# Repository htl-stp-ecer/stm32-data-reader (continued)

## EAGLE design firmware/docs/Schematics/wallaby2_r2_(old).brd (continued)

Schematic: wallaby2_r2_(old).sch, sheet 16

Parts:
C2, C3, C4, C5, C6, C7, C8, C9, C10, C11, C13, C19, C74: 0.1uF; 0603
C12, C73: 2.2uF; 0603
C16: 10uF; 0805-NO
C17, C18: 1uF; 0805-NO
D1: MBR0540; SOD-123
D2: MM3Z24VT1G; SMADIODE
D3: 1N4148; SOD-323
FB1, FB2, FB3, FB4: Ferrite; _0805MP
J9: 40PINFPCM4-1734839-0; 4-1734839-0
L1: 15uH; INDUCTOR_5X5MM_NR5040_NOTHERMALS
R1, R2, R3, R4, R5, R8: 10k; 0603
R6, R67, R72, R73: 0; 0603
R7: 47k; 0603
R15, R16: 12; 0805-NO
R70, R71: DNP; 0603
SJ1, SJ2: SOLDERJUMPER; SOLDERJUMPER_ARROW_NOPASTE
SJ3: -25mA; SOLDERJUMPER_CLOSEDWIRE
U1: TFP401; S-PQFP-G100
U2: 24LC02BT-I/OT; SOT23-5
U4: FAN5333BSX; SOT23-5
U31, U32, U33, U34: MOUNTINGHOLE3.0; MOUNTINGHOLE_3.0_PLATED
U$8: TSC2003; TSSOP16
X1: 47151-0001; HDMI_MOLEX_47151-0001_DIMLAYER

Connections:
5.0V: C13.1, R1.1, R3.2, R4.2, U2.4 (VCC), X1.18 (+5V)
24V: C17.1, C18.1, D1.C, D2.C, J9.2 (MS)
ACTIVE: D3.C, J9.31 (MS), U1.8 (SCDT)
AVDD: C9.1, C11.1, FB3.2, U1.82 (AVDD), U1.84 (AVDD), U1.88 (AVDD), U1.95 (AVDD)
B0: J9.21 (MS), U1.10 (QE0)
B1: J9.22 (MS), U1.11 (QE1)
B2: J9.23 (MS), U1.12 (QE2)
B3: J9.24 (MS), U1.13 (QE3)
B4: J9.25 (MS), U1.14 (QE4)
B5: J9.26 (MS), U1.15 (QE5)
B6: J9.27 (MS), U1.16 (QE6)
B7: J9.28 (MS), U1.17 (QE7)
CTL1: U1.40 (CTL1)
CTL2: U1.41 (CTL2)
CTL3: U1.42 (CTL3)
DISPEN: J9.34 (MS), U1.46 (DE)
G0: J9.13 (MS), U1.20 (QE8)
G1: J9.14 (MS), U1.21 (QE9)
G2: J9.15 (MS), U1.22 (QE10)
G3: J9.16 (MS), U1.23 (QE11)
G4: J9.17 (MS), U1.24 (QE12)
G5: J9.18 (MS), U1.25 (QE13)
G6: J9.19 (MS), U1.26 (QE14)
G7: J9.20 (MS), U1.27 (QE15)
GND: C2.2, C3.2, C4.2, C5.2, C6.2, C7.2, C8.2, C9.2, C10.2, C11.2, C12.2, C13.2, C16.1, C17.2, C18.2, C19.2, C73.2, C74.2, J9.3 (MS), J9.29 (MS), J9.36 (MS), R5.1, R15.2, R16.2, R72.2, R73.2, SJ2.1, U1.1 (DFO), U1.4 (PIXS), U1.5 (GND), U1.19 (OGND), U1.28 (OGND), U1.39 (GND), U1.45 (OGND), U1.58 (OGND), U1.68 (GND), U1.76 (OGND), U1.79 (AGND), U1.83 (AGND), U1.87 (AGND), U1.89 (AGND), U1.92 (AGND), U1.98 (PGND), U1.P$1 (TP), U1.P$2 (TP), U1.P$3 (TP), U1.P$4 (TP), U1.P$5 (TP), U1.P$6 (TP), U1.P$7 (TP), U1.P$8 (TP), U1.P$9 (TP), U1.P$10 (TP), U1.P$11 (TP), U1.P$12 (TP), U1.P$13 (TP), U1.P$14 (TP), U1.P$15 (TP), U1.P$16 (TP), U1.THERMAL (TP), U2.2 (GND), U2.5 (WP), U4.2 (GND), U$8.P$6 (6_GND), X1.2 (TX2_SHIELD), X1.5 (TX1_SHIELD), X1.8 (TX0_SHIELD), X1.11 (TXC_SHIELD), X1.17 (GND), X1.P$1 (GND), X1.P$2 (GND), X1.P$3 (GND), X1.P$4 (GND); also elsewhere on the board
HSYNC: J9.32 (MS), U1.48 (HSYNC)
LEDK: C19.1, D2.A, J9.1 (MSV), R16.1, SJ3.2, U4.3 (FB)
unnamed: U1.93 (RXC+), X1.10 (TXC+)
unnamed: U1.94 (RXC-), X1.12 (TXC-)
unnamed: U1.90 (RX0+), X1.7 (TX0+)
unnamed: U1.91 (RX0-), X1.9 (TX0-)
unnamed: U1.85 (RX1+), X1.4 (TX1+)
unnamed: U1.86 (RX1-), X1.6 (TX1-)
unnamed: U1.80 (RX2+), X1.1 (TX2+)
unnamed: U1.81 (RX2-), X1.3 (TX2-)
unnamed: R1.2, X1.19 (HOTPLUG)
unnamed: R67.1, U$8.P$7 (7_VBAT1)
unnamed: C73.1, C74.1, R6.2, U$8.P$9 (9_VREF)
unnamed: R71.2, R73.1, U$8.P$13 (13_A1)
unnamed: D1.A, L1.P$2 (2), U4.1 (SW)
unnamed: R15.1, SJ3.1
unnamed: D3.A, R8.1, U4.4 (SHDN)
unnamed: R70.2, R72.1, U$8.P$14 (14_A0)
OCK_INV: R5.2, SJ1.1, U1.100 (OCK_INV)
OVDD: C5.1, C6.1, C7.1, C8.1, FB2.2, U1.18 (OVDD), U1.29 (OVDD), U1.43 (OVDD), U1.57 (OVDD), U1.78 (OVDD)
PIXCLK: J9.30 (MS), U1.44 (ODCK)
PI_GPIO25: R7.2, U$8.P$10 (10_PEN); also elsewhere on the board
PI_I2C1_SCL: U$8.P$12 (12_SCL); also elsewhere on the board
PI_I2C1_SDA: U$8.P$11 (11_SDA); also elsewhere on the board
PVDD: C10.1, FB4.2, U1.97 (PVDD)
PWRDN: U1.2 (#PD)
PWRDN_O: U1.9 (#PDO)
R0: J9.5 (MS), U1.30 (QE16)
R1: J9.6 (MS), U1.31 (QE17)
R2: J9.7 (MS), U1.32 (QE18)
R3: J9.8 (MS), U1.33 (QE19)
R4: J9.9 (MS), U1.34 (QE20)
R5: J9.10 (MS), U1.35 (QE21)
R6: J9.11 (MS), U1.36 (QE22)
R7: J9.12 (MS), U1.37 (QE23)
SCL: R4.1, U2.1 (SCL), X1.15 (DCLK)
SDA: R3.1, U2.3 (SDA), X1.16 (DDAT)
ST: R2.1, SJ2.2, U1.3 (ST)
VCC_3V3: C4.1, C12.1, FB1.1, FB2.1, FB3.1, FB4.1, J9.4 (MS), R6.1, R7.1, R67.2, R70.1, R71.1, U$8.P$1 (1_VDD); also elsewhere on the board
VCC_5V0: C16.2, L1.P$1 (1), R8.2, U4.5 (VIN); also elsewhere on the board
VDDIO: C2.1, C3.1, FB1.2, R2.2, SJ1.2, U1.6 (DVDD), U1.7 (#STAG), U1.38 (DVDD), U1.67 (DVDD), U1.99 (RSVD)
VSYNC: J9.33 (MS), U1.47 (VSYNC)
X+: J9.37 (MS), U$8.P$2 (2_XP)
X-: J9.39 (MS), U$8.P$4 (4_XN)
Y+: J9.38 (MS), U$8.P$3 (3_YP)
Y-: J9.40 (MS), U$8.P$5 (5_XP)

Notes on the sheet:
DNP

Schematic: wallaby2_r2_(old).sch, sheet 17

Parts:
FID1, FID2, FID3, FID4, FID5, FID6: FIDUCIAL1X2.5; FIDUCIAL-1X2.5

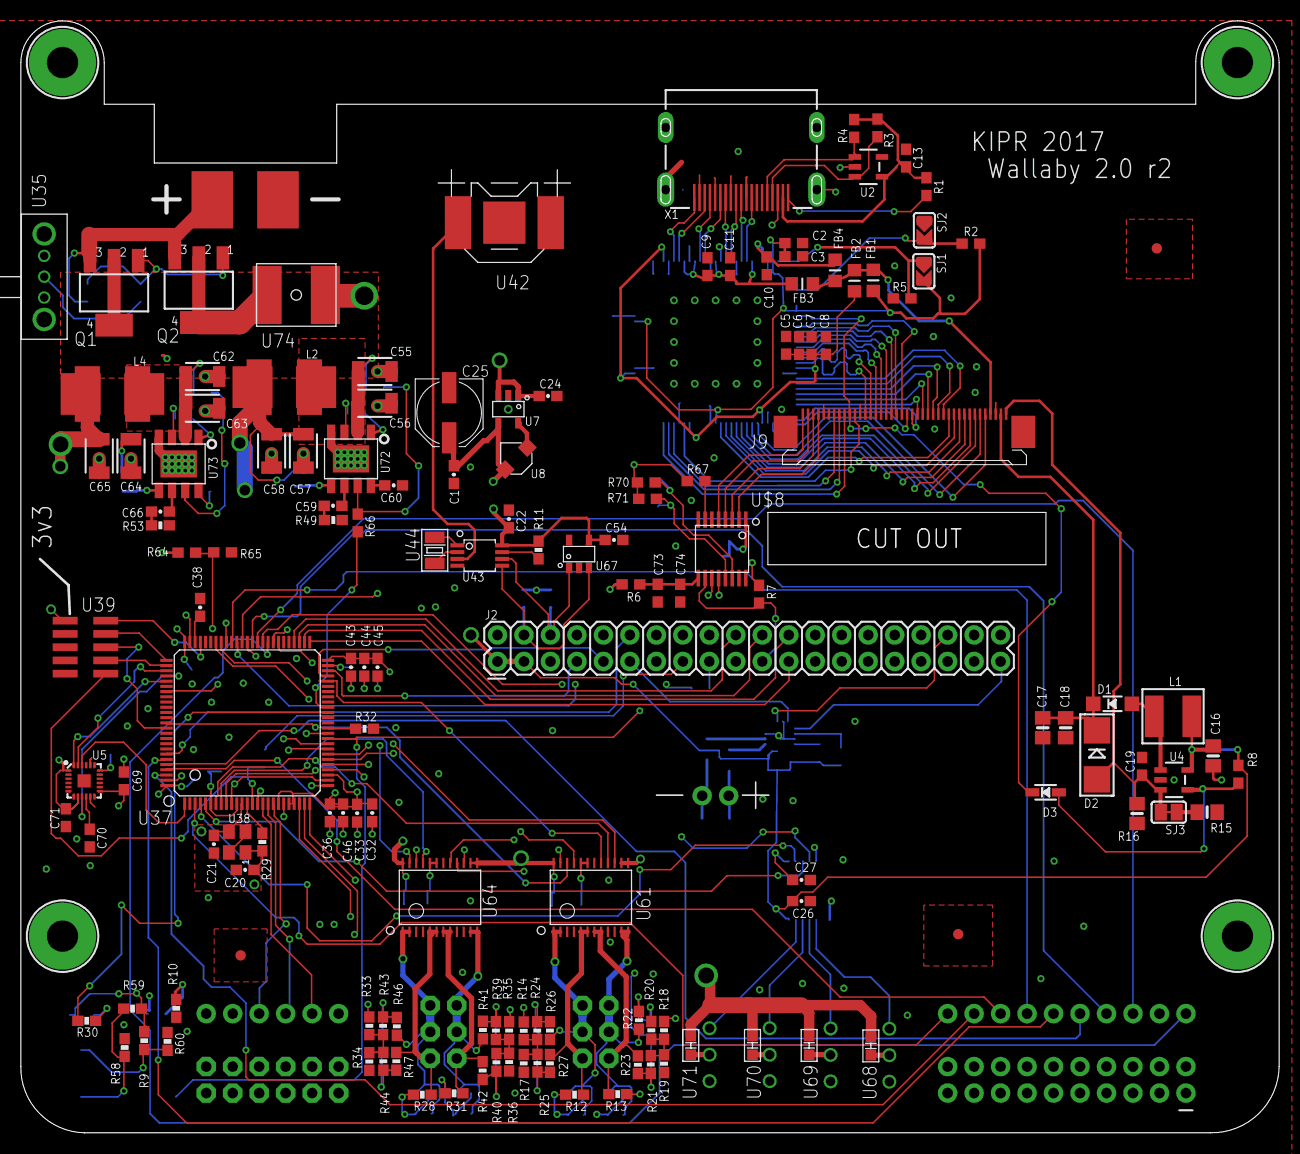
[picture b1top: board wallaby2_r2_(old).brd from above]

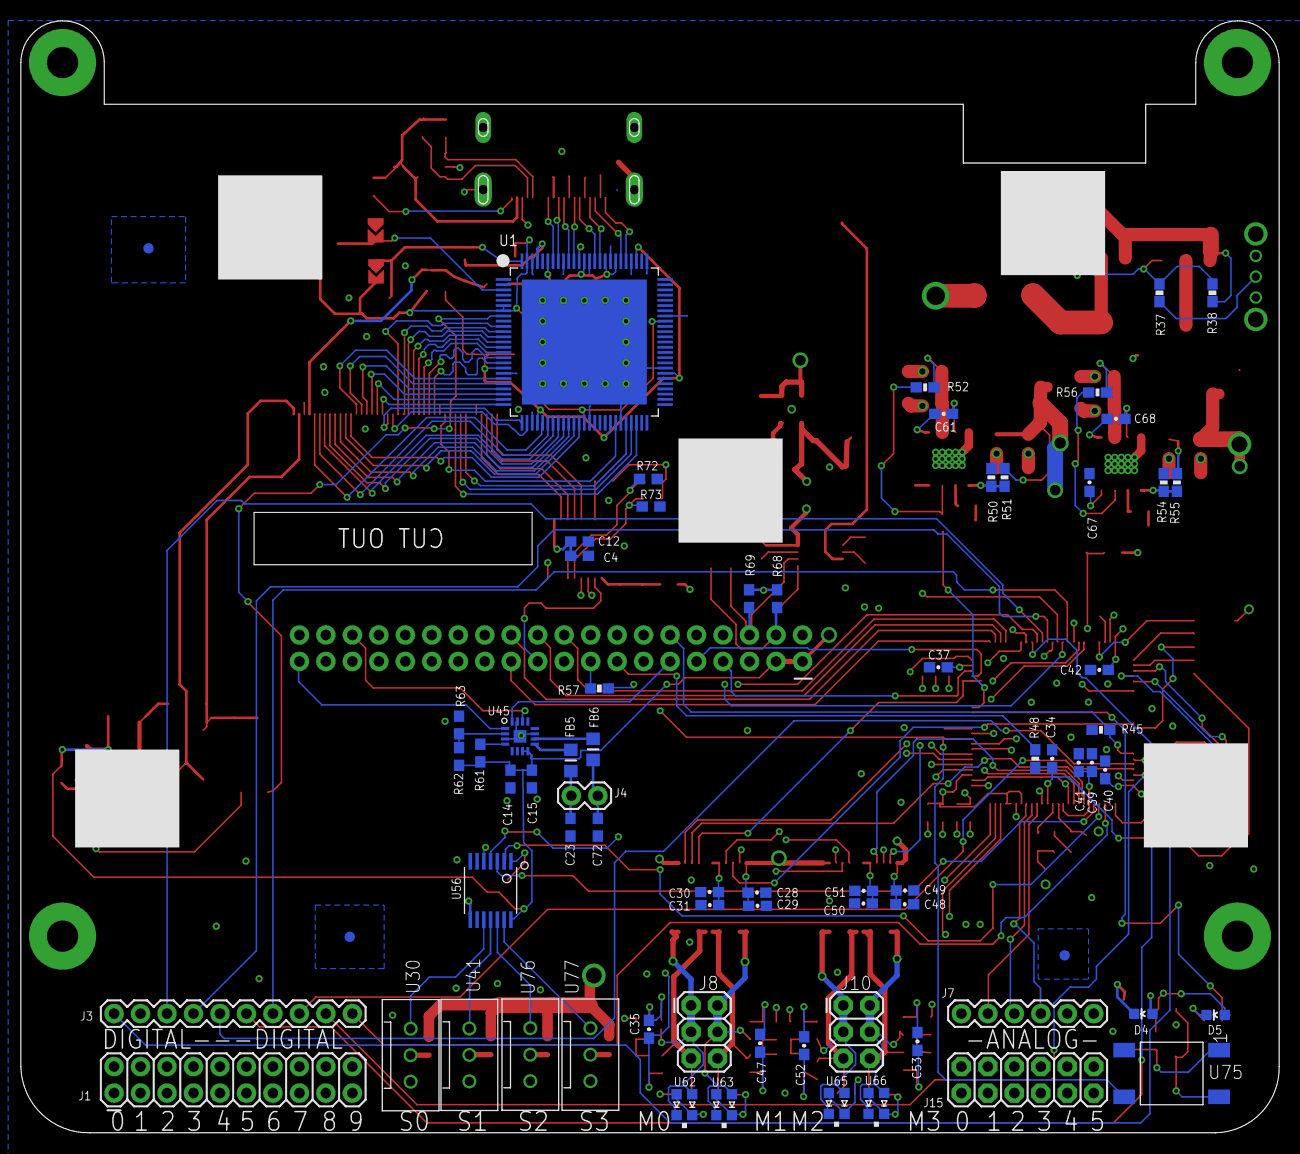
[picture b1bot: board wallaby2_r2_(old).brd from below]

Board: 6 copper layers, 120.7 x 106.7 mm, 222 parts (71 on the bottom side), 198 nets.

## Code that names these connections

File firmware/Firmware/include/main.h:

/* USER CODE BEGIN Header */
/**
  ******************************************************************************
  * @file           : main.h
  * @brief          : Header for main.c file.
  *                   This file contains the common defines of the application.
  ******************************************************************************
  * @attention
  *
  * Copyright (c) 2025 STMicroelectronics.
  * All rights reserved.
  *
  * This software is licensed under terms that can be found in the LICENSE file
  * in the root directory of this software component.
  * If no LICENSE file comes with this software, it is provided AS-IS.
  *
  ******************************************************************************
  */
/* USER CODE END Header */

/* Define to prevent recursive inclusion -------------------------------------*/
#ifndef __MAIN_H
#define __MAIN_H

#ifdef __cplusplus
extern "C" {
#endif

/* Includes ------------------------------------------------------------------*/
#include "stm32f4xx_hal.h"

/* Exported types ------------------------------------------------------------*/

/* Exported constants --------------------------------------------------------*/

/* Exported macro ------------------------------------------------------------*/

/* Exported functions prototypes ---------------------------------------------*/
void Error_Handler(void);


/* Private defines -----------------------------------------------------------*/
/*----------<user LED>----------*/
#define USER_LED_Pin GPIO_PIN_9
#define USER_LED_GPIO_Port GPIOE

/*----------<SPI>----------*/
//SPI for IMU
#define IMU_SPI_CS0_Pin GPIO_PIN_2
#define IMU_SPI_CS0_GPIO_Port GPIOE
#define IMU_SPI_CS1_Pin GPIO_PIN_3
#define IMU_SPI_CS1_GPIO_Port GPIOE
#define IMU_SPI_SCK_Pin GPIO_PIN_10
#define IMU_SPI_SCK_GPIO_Port GPIOC
#define IMU_SPI_MISO_Pin GPIO_PIN_11
#define IMU_SPI_MISO_GPIO_Port GPIOC
#define IMU_SPI_MOSI_Pin GPIO_PIN_12
#define IMU_SPI_MOSI_GPIO_Port GPIOC

//SPI communication with the Raspberry Pi
#define PI_SPI_CS_Pin GPIO_PIN_12
#define PI_SPI_CS_GPIO_Port GPIOB
#define PI_SPI_SCK_Pin GPIO_PIN_13
#define PI_SPI_SCK_GPIO_Port GPIOB
#define PI_SPI_MISO_Pin GPIO_PIN_14
#define PI_SPI_MISO_GPIO_Port GPIOB
#define PI_SPI_MOSI_Pin GPIO_PIN_15
#define PI_SPI_MOSI_GPIO_Port GPIOB

/*----------<UART>----------*/
//UART communication with the Raspberry Pi
#define PI_UART_TX_Pin GPIO_PIN_10
#define PI_UART_TX_GPIO_Port GPIOB

#define PI_UART_RX_Pin GPIO_PIN_11
#define PI_UART_RX_GPIO_Port GPIOB

/*----------<Servo>----------*/
//6V0 Enable (Servo Voltage Source)
#define SERVO_6V0_ENABLE_Pin GPIO_PIN_10
#define SERVO_6V0_ENABLE_GPIO_Port GPIOE

//servo PWM pins
#define S0_PWM_Pin GPIO_PIN_8
#define S0_PWM_GPIO_Port GPIOC

#define S1_PWM_Pin GPIO_PIN_7
#define S1_PWM_GPIO_Port GPIOC

#define S2_PWM_Pin GPIO_PIN_6
#define S2_PWM_GPIO_Port GPIOE

#define S3_PWM_Pin GPIO_PIN_5
#define S3_PWM_GPIO_Port GPIOE

/*----------<motor>----------*/
//motor PWM pins
#define MOT0_PWM_Pin GPIO_PIN_8
#define MOT0_PWM_GPIO_Port GPIOA

#define MOT1_PWM_Pin GPIO_PIN_9
#define MOT1_PWM_GPIO_Port GPIOA

#define MOT2_PWM_Pin GPIO_PIN_10
#define MOT2_PWM_GPIO_Port GPIOA

#define MOT3_PWM_Pin GPIO_PIN_6
#define MOT3_PWM_GPIO_Port GPIOC

//motor direction pins
//motor 0 direction pins
#define MOT0_D0_Pin GPIO_PIN_1
#define MOT0_D0_GPIO_Port GPIOD
#define MOT0_D1_Pin GPIO_PIN_7
#define MOT0_D1_GPIO_Port GPIOD

//motor 1 direction pins
#define MOT1_D1_Pin GPIO_PIN_13
#define MOT1_D1_GPIO_Port GPIOC
#define MOT1_D0_Pin GPIO_PIN_15
#define MOT1_D0_GPIO_Port GPIOE

//motor 2 direction pins
#define MOT2_D0_Pin GPIO_PIN_14
#define MOT2_D0_GPIO_Port GPIOC
#define MOT2_D1_Pin GPIO_PIN_15
#define MOT2_D1_GPIO_Port GPIOC

//motor 3 direction pins
#define MOT3_D0_Pin GPIO_PIN_10
#define MOT3_D0_GPIO_Port GPIOD
#define MOT3_D1_Pin GPIO_PIN_11
#define MOT3_D1_GPIO_Port GPIOD


/*----------<digital inputs>----------*/
//build in button
#define Button_Pin GPIO_PIN_0
#define Button_GPIO_Port GPIOB

//digital Ports
#define DIN0_Pin GPIO_PIN_12
#define DIN0_GPIO_Port GPIOD

#define DIN1_Pin GPIO_PIN_13
#define DIN1_GPIO_Port GPIOD

#define DIN2_Pin GPIO_PIN_14
#define DIN2_GPIO_Port GPIOD

#define DIN3_Pin GPIO_PIN_15
#define DIN3_GPIO_Port GPIOD

#define DIN4_Pin GPIO_PIN_9
#define DIN4_GPIO_Port GPIOB

#define DIN5_Pin GPIO_PIN_8
#define DIN5_GPIO_Port GPIOB

#define DIN6_Pin GPIO_PIN_9
#define DIN6_GPIO_Port GPIOC

#define DIN7_Pin GPIO_PIN_0
#define DIN7_GPIO_Port GPIOE

#define DIN8_Pin GPIO_PIN_1
#define DIN8_GPIO_Port GPIOE

#define DIN9_Pin GPIO_PIN_4
#define DIN9_GPIO_Port GPIOE

/*----------<analog inputs>----------*/
//battery voltage
#define VCC_BATT_SENSOR_Pin GPIO_PIN_0
#define VCC_BATT_SENSOR_GPIO_Port GPIOC

//analog ports
#define AIN0_Pin GPIO_PIN_1
#define AIN0_GPIO_Port GPIOB

#define AIN1_Pin GPIO_PIN_1
#define AIN1_GPIO_Port GPIOC

#define AIN2_Pin GPIO_PIN_2
#define AIN2_GPIO_Port GPIOC

#define AIN3_Pin GPIO_PIN_3
#define AIN3_GPIO_Port GPIOC

#define AIN4_Pin GPIO_PIN_4
#define AIN4_GPIO_Port GPIOC

#define AIN5_Pin GPIO_PIN_5
#define AIN5_GPIO_Port GPIOC

//motor BEMF pin
//motor 0 BEMF pins
#define MOT0_BEMFH_Pin GPIO_PIN_0
#define MOT0_BEMFH_GPIO_Port GPIOA
#define MOT0_BEMFL_Pin GPIO_PIN_1
#define MOT0_BEMFL_GPIO_Port GPIOA

//motor 1 BEMF pins
#define MOT1_BEMFH_Pin GPIO_PIN_2
#define MOT1_BEMFH_GPIO_Port GPIOA
#define MOT1_BEMFL_Pin GPIO_PIN_3
#define MOT1_BEMFL_GPIO_Port GPIOA

//motor 2 BEMF pins
#define MOT2_BEMFH_Pin GPIO_PIN_4
#define MOT2_BEMFH_GPIO_Port GPIOA
#define MOT2_BEMFL_Pin GPIO_PIN_5
#define MOT2_BEMFL_GPIO_Port GPIOA

//motor 3 BEMF pins
#define MOT3_BEMFH_Pin GPIO_PIN_6
#define MOT3_BEMFH_GPIO_Port GPIOA
#define MOT3_BEMFL_Pin GPIO_PIN_7
#define MOT3_BEMFL_GPIO_Port GPIOA


#ifdef __cplusplus
}
#endif

#endif /* __MAIN_H */

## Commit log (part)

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2025-07-15 Init
2025-07-16 Added pub/sub of spi values
2025-08-19 Add .gitignore and update LCM publishing logic
2025-08-19 stfu
2025-09-10 Added dev container
2025-09-11 Update Dockerfile to streamline package installation and add .name file
2025-09-13 LCM-Data writer and tests
2025-09-25 Added systemd service to auto start
2025-09-25 Added battery
2025-10-01 Enhance logging and add battery migration XML files
2025-10-01 unified routes
2025-10-16 made bemf readable (there was a problem with bemf not being displayed. Updated docker cause there were problems with the certificates
2025-10-16 Add quaternion definitions and update temperature index in pi_buffer.h
2025-10-16 Add quaternion support to DataPublisher and LcmBroker, update SPI interface
2025-11-13 Add BEMF reset command support in CommandSubscriber and DeviceController
2025-11-20 Add CPU temperature publishing and logging to DataPublisher and Application
2026-01-02 added imu accuracy
2026-01-02 removed debug logging in INFO!!
2026-01-27 added deploy
2026-01-29 lcm offline capabilities
2026-01-29 added license and readme
2026-01-31 added spi update limit back
2026-02-04 supporting active braking & shutdown flags
2026-02-05 refactor: remove motor stop command handling and update shutdown flag logic
2026-02-07 feat: add timestamp handling for command messages in CommandSubscriber
2026-02-11 refactor: remove Spi.hpp and refactor Types.h into modular headers
2026-02-14 refactor: streamline SPI read process and optimize CommandSubscriber motor control logic
2026-02-14 feat: add SpiMock support for tests
2026-02-22 Remove LCM-related autogenerated files and motor PID tuning script.
    Deleted all LCM-generated Python files, type definitions, and init files under `lcm-messages` and `pythonTest/exlcm`. Additionally, removed the `motor_pid_tuning.py` script and its related file `quat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
2026-02-22 refactor: rename motor publish variables and update `motorPower` channel definition
    Renamed variables for clarity in `DataPublisher.cpp` and updated the `motorPower` channel definition to reflect "power" instead of "value".
2026-02-25 Add support for IMU orientation matrix configuration
    Introduced functionality to set IMU gyro and compass orientation matrices via SPI. Added necessary LCM message type, command handlers, and updates to device controllers and services to manage these m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
2026-02-26 Add support for orientation matrix handling and SPI improvements
    This commit introduces handling for `orientation_matrix_t` in `LcmBroker` subscriptions and adds corresponding mock methods in `MockSpi`. Additionally, it refactors SPI transfer logic to use fixed-si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
2026-02-26 feat: add axis remapping for sensor data in world frame
    Introduced support for body-to-world axis remapping in sensor data. Added `AxisRemap` utility, command handling in `CommandSubscriber`, and integration with `DataPublisher` to ensure IMU data outputs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
2026-02-28 feat: add heading data publishing and support
    Added handling for IMU heading data, including transmission through SPI, publishing via `DataPublisher`, and a corresponding new test case. Updated `DeviceTypes`, `Channels`, and SPI buffer structure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
2026-03-01 Transition to "raccoon" namespace for messaging and data types
    Replaced all occurrences of "exlcm" with "raccoon" for message structures and namespaces, ensuring consistency across the codebase. Removed unused code, added deduplication support for publishes, and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
2026-03-01 Refactor scripts and tests: restart services in `install.sh`, remove unused MockSpi methods, and enhance ccache handling in builds and CI
2026-03-01 Remove deprecated SPI buffer definitions and integrate ADC and IMU calibration modules
    - Deleted unused `pi_buffer.h` and related SPI buffer structures.
    - Added ADC initialization and sensor handling (`adcInit.c`, `adcPorts-batteryVoltage.c`).
    - Incorporated accelerometer auto-calibration headers (`accel_auto_cal.h`) from motion driver library.
    - Introduced MPU9250 example for IMU calibration documentation.
    - Updated `.gitignore` and `.gitattributes` for build and text file handling.
2026-03-01 Fix typo in motor mode constant, reorganize `install.sh` for reader installation, and use Docker for firmware builds and CI
    - Corrected `MOT_MODE_PASSIV_BREAK` typo to `MOT_MODE_PASSIV_BRAKE`.
    - Reorganized `install.sh` to ensure correct ordering of flashing firmware and uploading reader binary.
    - Switched firmware build process to Docker in both `build.sh` and CI, enabling caching and simplifying the toolchain setup.
2026-03-01 Refactor LCM handling and improve workflow artifact staging
    Replaces raw `lcm::LCM` instances with `std::unique_ptr` to fix potential use-after-free issues and improve safety. Updates GitHub workflow to stage and organize firmware artifacts in a temporary fol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
2026-03-01 Optimize GitHub Actions caching for firmware and reader builds
    - Add dedicated cache for firmware build directory to improve build performance.
    - Update reader build cache key to ensure proper restoration and handling.
2026-03-01 Switch GitHub Actions runners to self-hosted for all build and release workflows
2026-03-01 Update firmware build step in GitHub Actions to separate `build` and `up` commands
2026-03-01 Integrate compass support into IMU module
    - Added compass initialization and data handling in IMU functions.
    - Enabled compass fusion with gyro and accelerometer data.
    - Updated orientation and scale setup for compass calibration.
    - Adjusted sensor sampling rates and FIFO configuration to include compass data.
    - Improved timestamp handling and compass velocity calculations.
2026-03-01 Remove MPU9250 sensor-specific headers and integrate generic IMU support
    - Deleted MPU9250-specific configuration, DMP, and register map headers.
    - Added generic IMU calibration, data handling, and setup modules (`imu_calibration.c`, `imu_data.c`, `imu_setup.c`).
    - Refactored IMU orientation and scaling management to support multiple sensor platforms.
    - Updated IMU module to handle sensor fusion and improved sample rate synchronization.
    - Adjusted SPI configuration for IMU initialization.
2026-03-02 Add support for subscription options and improve publishing reliability
    Introduced `raccoon::SubscribeOptions` to enable subscription customization, including reliable subscriptions for critical commands. Updated several `publish` calls to `publishRetained` for improved 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
2026-03-02 fix: correct signed/unsigned handling in `putInt64` for reliable transport
2026-03-02 update: modify `raccoon-transport` implementation
2026-03-03 Replace install.sh with install.py and adjust timing parameters
    The Bash installation script was replaced with an equivalent Python script for better maintainability and readability. Additionally, increased spin loop delay in LcmBroker and main loop delay in Conf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
2026-03-03 Replace `install.sh` with `install.py` in release workflow
2026-03-07 Remove 9-axis sensor fusion and clean up IMU codebase
    Eliminated unused 9-axis fusion logic, including related headers and functions, to streamline IMU functionality. Adjusted quaternion handling to use the updated 6-axis data flow and improved code sty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
2026-03-07 Increase filtering alpha for battery voltage smoothing in SPI modules
2026-03-07 Add shutdown sequence for clearing motor and servo commands
    - Implemented logic to clear motor and servo states when enabling shutdown to prevent stale state reactivation.
    - Added test cases to validate shutdown behavior for both enabled and disabled states.
2026-03-13 Refactor channels: remove unused IMU and BEMF commands, add screen and vision support, and define motor relative command
2026-03-13 Disable calibration flash writes to resolve main loop blocking and refactor servo position to use degrees instead of raw values
2026-03-13 Simplify servo position to PWM conversion logic and update documentation
2026-03-14 Refactor BEMF measurement logic to per-motor ADC configuration
    Simplified BEMF logic by reducing ADC channels per motor to two and added dynamic per-motor ADC reconfiguration. Updated sampling intervals for faster measurements, introduced motor-specific median f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
2026-03-14 Refactor IMU heading logic and disable 9-axis fusion
    Disabled 9-axis sensor fusion initialization and adjusted IMU heading calculation to use DMP quaternion directly. Simplified logic to compute heading with higher precision and replaced deprecated inv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
2026-03-15 Add STM32 odometry system with kinematics and reset support
    Integrated STM32-side odometry system using dead reckoning with BEMF and IMU data. Added configuration handling for kinematics matrices and encoder calibration ticks, as well as odometry reset capabi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
2026-03-23 Add motor trajectory planning (MTP) test script and enhancements
    Added a new Python test script to analyze motor trajectory planning (MTP) with position control and test scenarios. Implemented significant firmware updates including a debounce for position changes,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
2026-04-07 chore: add COPYING file with copyright notice
2026-04-07 docs: rewrite README with branding, firmware section, cleaner architecture
2026-04-07 docs: add CONTRIBUTING.md
2026-04-07 docs: replace text architecture diagram with SVG
2026-04-07 docs: redesign architecture SVG with two explicit lanes for clarity
2026-04-10 updated transport
2026-04-14 servos dont instantly enable after a fully disable
2026-05-15 channel / transport
2026-05-18 feat: add BEMF feature flags and calibration storage updates
2026-05-18 feat: add synthetic motor refresh for BEMF disabled state
2026-05-18 feat: implement STM32 health and heartbeat monitoring with shutdown logic
2026-05-23 unified servo state into a state struct
2026-05-23 chore: update submodule URL and change CI environment to ubuntu-latest
2026-05-23 chore: use HTTPS for public submodule checkout
2026-05-23 feat(motor): add setMotorState method to manage motor states
2026-05-25 chore(pi_buffer): increment transfer version to 19
2026-05-25 chore: update hash in raccoon-transport file
2026-05-25 fix(flash_wombat): update flashing command to use sector erase for better reliability
2026-05-26 fix(ReliableSubscriber): make apiMutex parameter optional for improved flexibility
2026-05-29 feat(Transport): enhance transport stats with latency and callback metrics
2026-06-02 fix(watchdog): UART heartbeat warn-only, not fatal
    Application::checkStm32Heartbeat() used to terminate the service after
    12s without a UART heartbeat. The STM32 firmware periodically writes
    calibration data to flash (e.g. "[CAL] Saving 124 bytes to flash sector
    12"), which disables UART TX interrupts for >12s while SPI/DMA keeps
    flowing. Result: the reader killed itself in a steady ~30s loop even
    though sensors were live, causing every Pi-side `raccoon run` probe to
2026-06-02 fix(install): enable systemd-logind linger for runtime user
    Without linger=yes for the runtime user, every SSH disconnect ends the
    user's last session and systemd tears down user@<uid>.service. That
    teardown was wiping /dev/shm/raccoon_ring_* files even with
    RemoveIPC=no in logind.conf (verified via system-wide unlinkat trace on
    Pi 2026-06-02 — systemd processes accounted for ~150 unlinkat calls per
    raccoon run). With files gone, the next subscriber sees an empty
2026-06-02 bump(raccoon-transport): rrb_reader_recv NULL-guard
    Pulls in raccoon-transport f41e1a9 (branch
    fix/rrb-reader-recv-null-guard) which adds defensive r->base/r->hdr
    NULL checks in rrb_reader_recv plus a reproducer test suite. Fixes a
    production SIGSEGV (~once per 30s) where rrb_reader_recv dereferenced
    NULL r->hdr after reader_reopen_if_unlinked() detached without
    re-attaching.
2026-06-02 fix(systemd): drop ProtectSystem/ProtectHome (mount namespace clone)
    ProtectSystem=, ProtectHome=, and PrivateTmp= each cause systemd to
    clone /proc/self/ns/mnt for the service. Within the clone, /dev/shm is
    mounted MS_SLAVE relative to the host's tmpfs, so the
    /dev/shm/raccoon_ring_* files the reader creates are invisible to every
    other process on the host. The libstp probe sees an empty /dev/shm and
    times out waiting for IMU heading / BEMF / battery.
2026-06-06 feat: enhance raccoon transport with placeholder file creation and dynamic ring resizing
2026-06-22 refactor: improve logging and watchdog timing for motor control loop
